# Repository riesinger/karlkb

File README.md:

# KarlKB

The KarlKB is a wireless, split, 6x3+2 mechanical keyboard.
It features:

- nice!nano v2 microcontrollers (wireless, running [ZMK](https://github.com/riesinger/zmk-config))
- pads & through holes for a JST battery connector (or just solder it directly to the pads)
- a power switch
- a reset buttons
- 3 rows with 6 keys each and 2 thumb keys per half
- _no OLED_ ⚡
- _no RGB anywhere_ ⚡️
- _no TRRS jacks_ 📶

It is in fact my first custom keyboard and is currently still **WIP**.

## Hardware

The PCB layout is built with [Ergogen](https://github.com/ergogen/ergogen). The [`karlkb.yaml`](./karlkb.yaml) file is used as input.
The generated PCB layout is then routed with KiCad (6 and above).

To generate the PCB files with Ergogen, do

```sh
cd ergogen
npm install
node src/cli.js ../karlkb.yaml
```

You should now see and `output` folder, which contains a KiCad PCB. Route this PCB and send it off to be manufactured.

## Software

This keyboard uses ZMK as its firmware. See my [zmk-config](https://github.com/riesinger/zmk-config) repository for the corresponding configuration.

## Thanks to

- [Ben Vallack](https://github.com/benvallack) for exposing me to Ergogen (even though his tutorial is not really comprehensive 😉)
- [The Ergogen devs](https://github.com/ergogen/ergogen/graphs/contributors). Without them, these keys would never have been straight!
- [The ZMK devs](https://github.com/zmkfirmware/zmk/graphs/contributors) for providing an awesome and customizable wireless firmware
- [Josef Adamčík](https://github.com/josefadamcik) for my first ever wireless split keyboard, the [Sofle](https://github.com/josefadamcik/SofleKeyboard)
- [Anarion](https://github.com/anarion80) for the [Porcupine](https://github.com/anarion80/porcupine) keyboard. This is basically what tought me to use Ergogen. This keyboard is also using his fork with added footprints.

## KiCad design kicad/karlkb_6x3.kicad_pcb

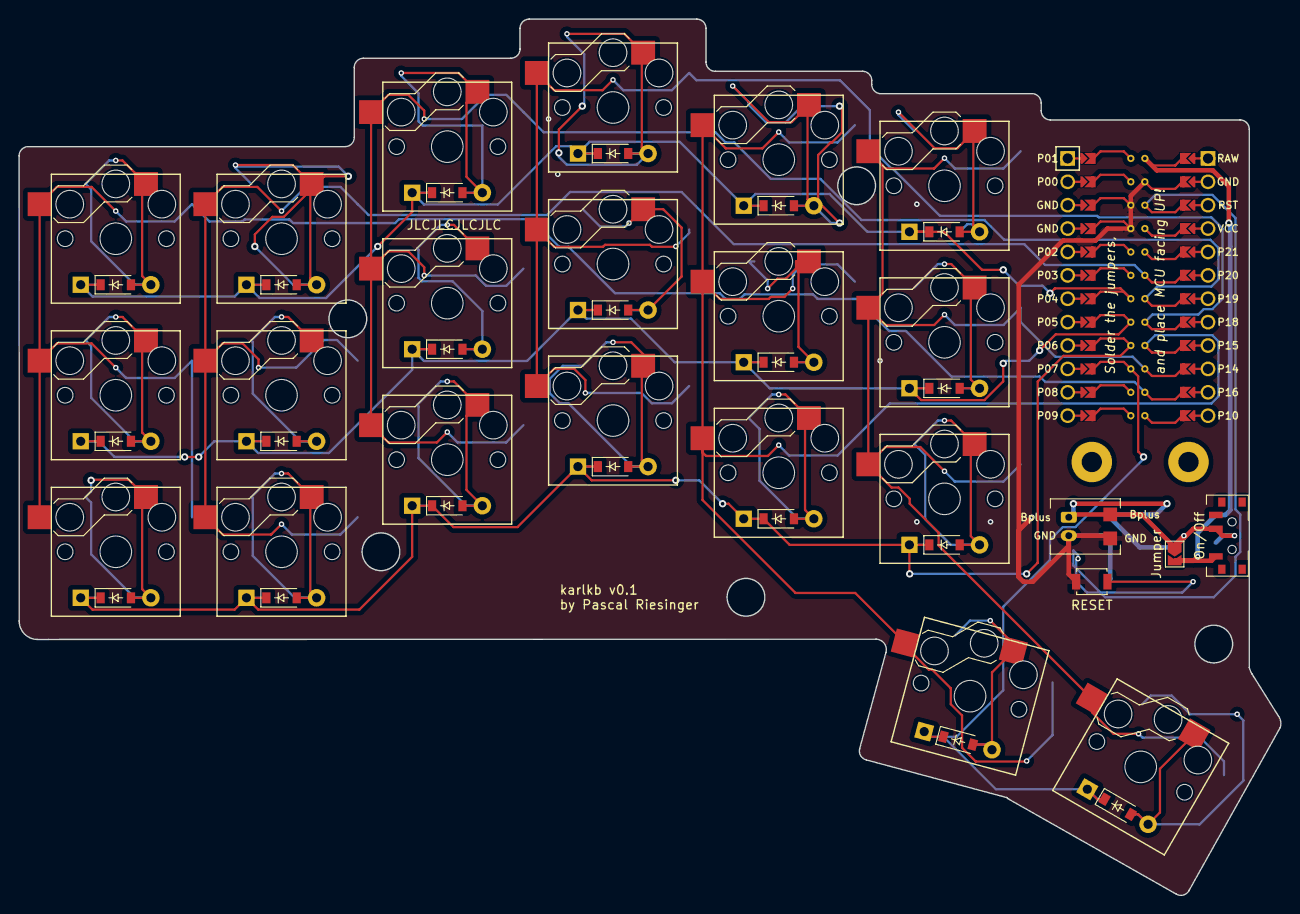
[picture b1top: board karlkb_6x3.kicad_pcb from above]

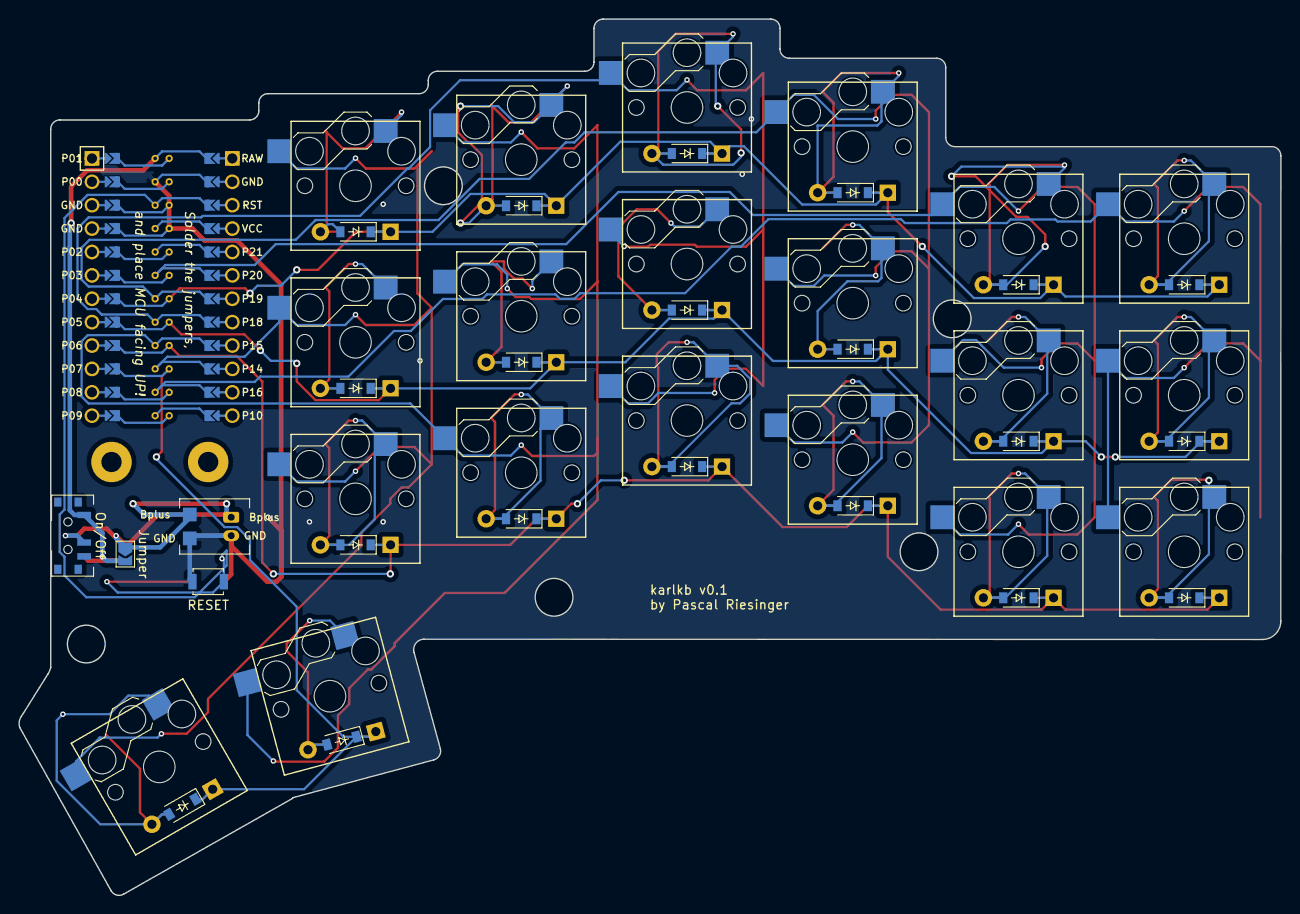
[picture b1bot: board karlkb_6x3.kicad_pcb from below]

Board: 2 copper layers, 137.0 x 95.2 mm, 51 parts (2 on the bottom side), 34 nets.

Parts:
D1, D2, D3, D4, D5, D6, D7, D8, D9, D10, D11, D12, D13, D14, D15, D16, D17, D18, D19, D20: D_SOD-123; SOD-123
J1, J2: Jumper; SolderJumper-2_P1.3mm_Open_TrianglePad1.0x1.5mm
MCU1: ProMicro
PAD1, PAD2: SMDPad
S1, S2, S3, S4, S5, S6, S7, S8, S9, S10, S11, S12, S13, S14, S15, S16, S17, S18, S19, S20: PG1350
_2: bat2p0
_3: SW_SPDT_PCM12
_4_B, _4_F: SW_Push; SW_SPST_B3U-1000P
_73, _74: hole; Through Hole

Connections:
Bplus: J1.1, J2.1, PAD1.1, _2.1, _3.2
GND: MCU1.2, MCU1.21, MCU1.22, PAD2.1, _2.2, _4_B.2
P4: D3.1, D3.2, D6.1, D6.2, D9.1, D9.2, D12.1, D12.2, D15.1, D15.2, D18.1, D18.2, MCU1.18
P5: D2.1, D2.2, D5.1, D5.2, D8.1, D8.2, D11.1, D11.2, D14.1, D14.2, D17.1, D17.2, MCU1.17
P6: D1.1, D1.2, D4.1, D4.2, D7.1, D7.2, D10.1, D10.2, D13.1, D13.2, D16.1, D16.2, MCU1.16
P7: D19.1, D19.2, D20.1, D20.2, MCU1.15
P14: MCU1.10, S16.2, S17.2, S18.2, S20.2
P15: MCU1.9, S13.2, S14.2, S15.2, S19.2
P16: MCU1.11, S1.2, S2.2, S3.2
P18: MCU1.8, S10.2, S11.2, S12.2
P19: MCU1.7, S7.2, S8.2, S9.2
P20: MCU1.6, S4.2, S5.2, S6.2
RAW: J1.2, J2.2, MCU1.1, _3.1
RST: MCU1.3, _4_B.1
far_thumb: D20.1, D20.2, S20.1
home_thumb: D19.1, D19.2, S19.1
index_bottom: D13.1, D13.2, S13.1
index_home: D14.1, D14.2, S14.1
index_top: D15.1, D15.2, S15.1
inner_bottom: D16.1, D16.2, S16.1
inner_home: D17.1, D17.2, S17.1
inner_top: D18.1, D18.2, S18.1
middle_bottom: D10.1, D10.2, S10.1
middle_home: D11.1, D11.2, S11.1
middle_top: D12.1, D12.2, S12.1
outer_bottom: D1.1, D1.2, S1.1
outer_home: D2.1, D2.2, S2.1
outer_top: D3.1, D3.2, S3.1
pinky_bottom: D4.1, D4.2, S4.1
pinky_home: D5.1, D5.2, S5.1
pinky_top: D6.1, D6.2, S6.1
ring_bottom: D7.1, D7.2, S7.1
ring_home: D8.1, D8.2, S8.1
ring_top: D9.1, D9.2, S9.1

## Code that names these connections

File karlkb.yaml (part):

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          ref: matrix_pinky_top
          shift: [-5,8]
        params:
          net: pinky_top
      via_P20_2:
        what: simple_via
        adjust:
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          ref: matrix_pinky_home
          shift: [0,8.5]
        params:
          net: pinky_home
      via_P20_3:
        what: simple_via
        adjust:
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          ref: matrix_pinky_bottom
          shift: [0,8.5]
        params:
          net: pinky_bottom
      via_P19_1:
        what: simple_via
        adjust:
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
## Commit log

2023-03-02 Initial commit 🚀
2024-10-31 Start working on v0.2
